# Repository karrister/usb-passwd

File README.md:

USB-passwd
=============

Project for a small USB device that attaches directly to the USB-A port of a PC.

The device acts as a USB HID/keyboard. With the press of a button, it inserts the passphrase,
configured by the user on the memory of the PIC microcontroller through USB-UART interface.

The device has two physical buttons, and thus supports two separate passwords to be configured.

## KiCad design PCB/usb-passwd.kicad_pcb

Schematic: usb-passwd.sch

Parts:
C1, C2: CSMALL
C3, C4: C
D1: DBG
D2: USER
K1: UART
P1: ICSP
P2: USB
P3: SW1
P4: SW2
R1, R2, R3: R
U1: PIC18F14K50
X1: CRYSTAL-SMD

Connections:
+5V: C3.2, P1.2, P2.1, R3.2, U1.1 (Vdd)
/BUTTON1: P3.1, U1.13 (RB4/AN10/SDI/SDA)
/BUTTON2: P4.1, U1.11 (RB6/SCK)
/D+: P1.4, P2.3, U1.19 (RA0/D+)
/D-: P1.5, P2.2, U1.18 (RA1/D-)
/DBG_LED: R1.1, U1.16 (RC0/AN4/INT0)
/OSC1: C2.2, U1.2 (RA5/OSC1), X1.3
/OSC2: C1.2, U1.3 (RA4/OSC2), X1.1
/UART_RX: K1.2 (PM), U1.12 (RB5/AN11/RX)
/UART_TX: K1.1, U1.10 (RB7/TX)
/USER_LED: R2.1, U1.15 (RC1/AN5/INT1)
/Vpp: P1.1, R3.1, U1.4 (RA3/MCLR)
GND: C1.1, C2.1, C3.1, C4.1, D1.2 (K), D2.2 (K), K1.3, P1.3, P2.4, P3.3, P4.3, U1.20 (Vss), X1.2 (GND), X1.4 (GND)
unnamed: D2.1 (A), R2.2
unnamed: D1.1 (A), R1.2
unnamed: C4.2, U1.17 (VUSB)

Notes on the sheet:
Oscillator
Connectors
User interface
Power

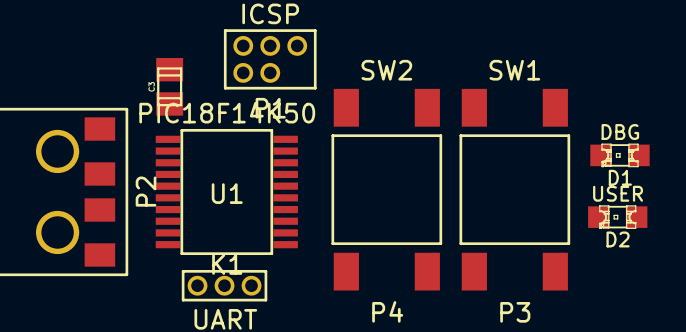
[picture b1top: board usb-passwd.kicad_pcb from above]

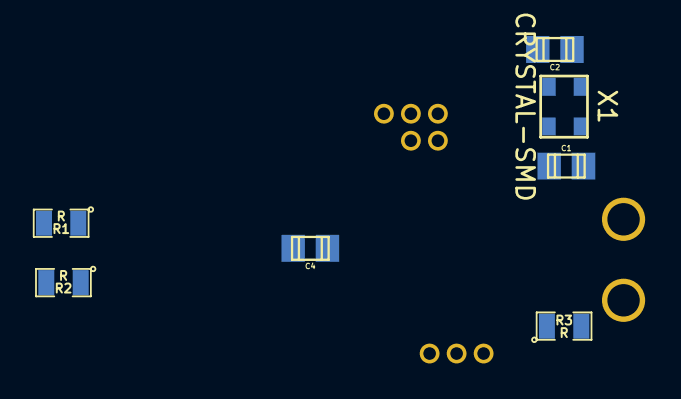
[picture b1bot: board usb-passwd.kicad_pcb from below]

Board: 2 copper layers, 16 parts (7 on the bottom side), 16 nets, no tracks yet.

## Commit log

2015-08-24 :tada: Added .gitattributes
2015-08-24 Initial commit
    Readme-file, directory structure.
2015-08-24 More dir structures
    Creating PCB kicad project, adding kicad submodule for shared parts.
2015-09-05 Some changes
2015-09-05 Updating to the latest submodules
2015-09-05 More schematics
    Schematics partly done
2015-09-05 Schematics finished
    Schematics are done
2015-09-05 Netlist started
2015-11-06 More netlist, footprint work
    Added more stuff to netlist, created some footprints.
2015-11-06 Adding ICSP, UART modules
    Adding layout footprints for ICSP and UART connectors.
2015-11-08 Added parts in submodule
2015-11-08 Netlist finished, started the layout
2015-11-08 Fixed typo, and updated the README
